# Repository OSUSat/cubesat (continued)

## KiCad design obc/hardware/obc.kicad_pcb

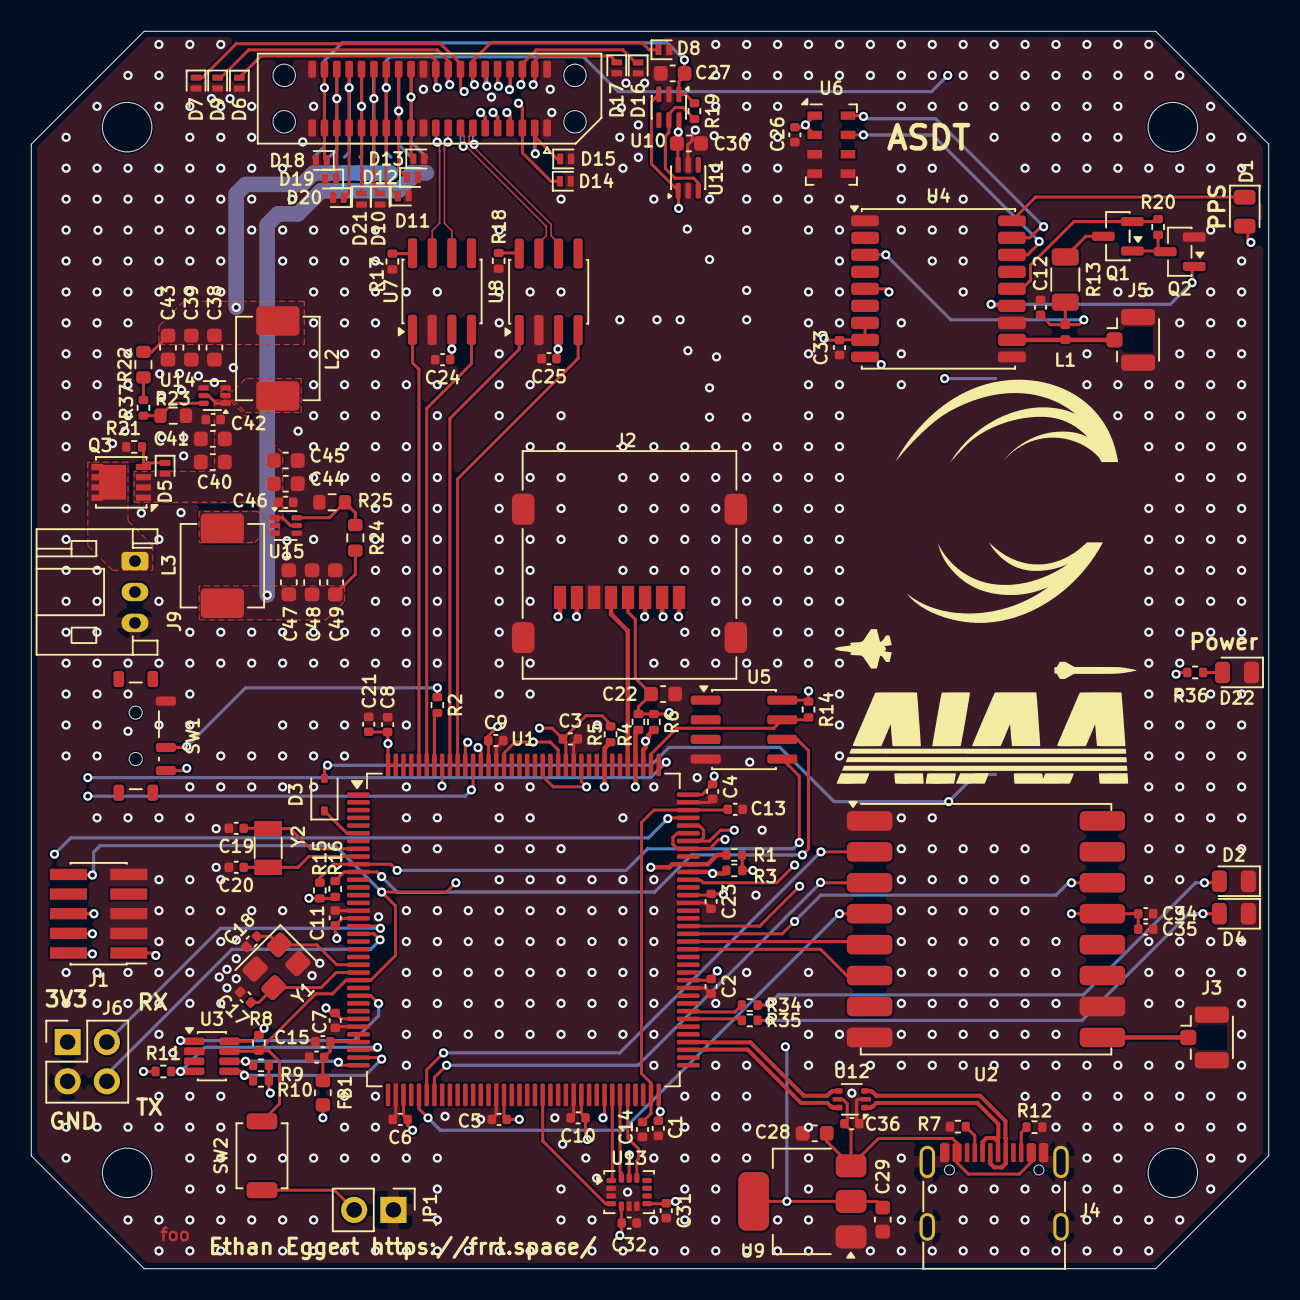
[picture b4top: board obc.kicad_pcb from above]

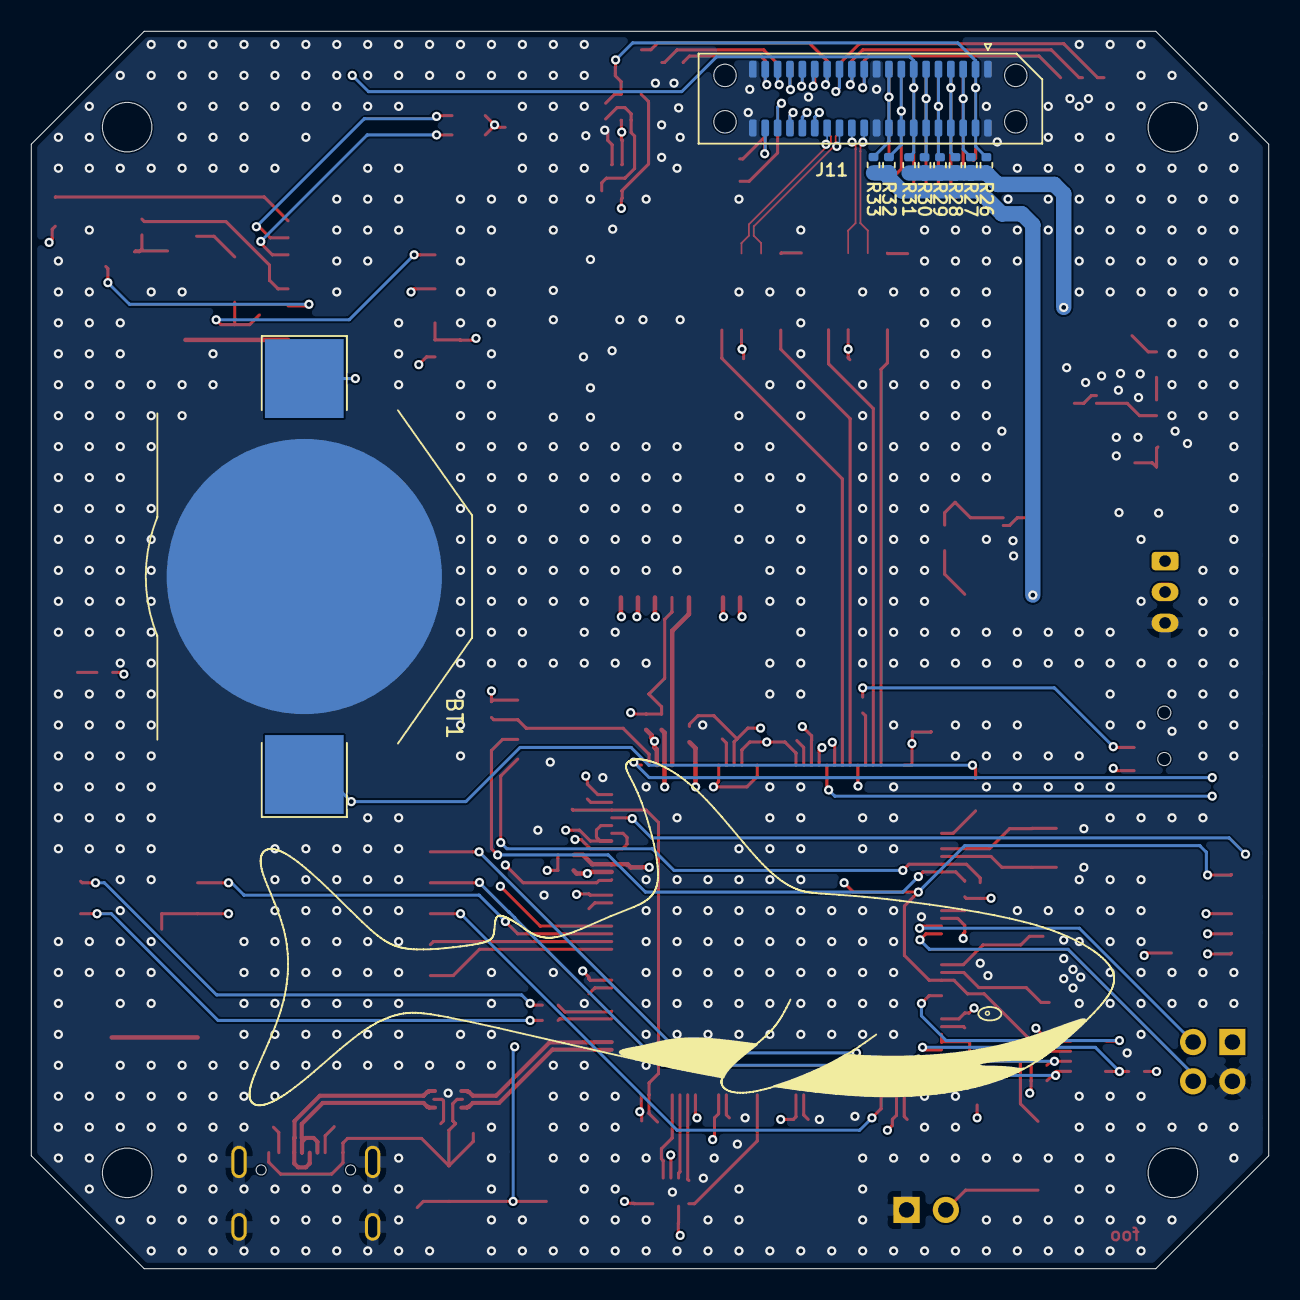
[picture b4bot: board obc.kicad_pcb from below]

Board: 4 copper layers, 80.0 x 80.0 mm, 148 parts (10 on the bottom side), 108 nets.

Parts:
BT1: CR2032; BatteryHolder_Keystone_3002_1x2032
C1, C2, C3, C4, C5, C6, C7, C8, C9, C10, C11, C15, C23, C24, C25, C26, C31, C32, C33, C34, C36, C42, C46: 100nF; C_0402_1005Metric
C12: 10nF; C_0402_1005Metric
C13, C14: 2.2uF; C_0402_1005Metric
C16, C35: 1uF; C_0402_1005Metric
C17, C18: 12pF; C_0402_1005Metric
C19, C20: 15pF; C_0402_1005Metric
C21: 4.7uF; C_0402_1005Metric
C22, C27, C28, C30, C40, C41, C44, C45: 10uF; C_0603_1608Metric
C29, C38, C39, C43, C47, C48, C49: 22u; C_0603_1608Metric
D1: White; LED_0805_2012Metric
D2: Red; LED_0805_2012Metric
D3: 1N5819WS; D_SOD-323
D4: Green; LED_0805_2012Metric
D5: D_TVS; D_SOD-882
D6, D7, D8, D9, D10, D11, D12, D13, D14, D15, D16, D17, D18, D19, D20, D21: D_Zener; D_SOD-882
D22: Yellow; LED_0805_2012Metric
FB1: 600R; L_0603_1608Metric
H1, H2, H3, H4: MountingHole; MountingHole_3.2mm_M3
J1: Conn_ARM_JTAG_SWD_10; PinHeader_2x05_P1.27mm_Vertical_SMD
J2: Micro_SD_Card; microSD_HC_Molex_47219-2001
J3, J5: Conn_Coaxial; U.FL_Hirose_U.FL-R-SMT-1_Vertical
J4: USB_C_Receptacle_USB2.0_16P; USB_C_Receptacle_G-Switch_GT-USB-7010ASV
J6: Conn_02x02_Odd_Even; PinHeader_2x02_P2.54mm_Vertical
J9: Conn_01x03; JST_PH_S3B-PH-K_1x03_P2.00mm_Horizontal
J10: Samtec_ERM8-020-XX.X-DV_2x20_P0.8mm_Terminal
J11: ERF8-020-09.0-L-DV-TR; Samtec_ERF8-020-XX.X-DV_2x20_P0.8mm_Socket
JP1: Jumper; PinHeader_1x02_P2.54mm_Vertical
L1: 27nH; L_0402_1005Metric
L2, L3: 1.5uH; L_Vishay_IHLP-2020
Q1: AO3401A; SOT-23
Q2: AO3400A; SOT-23
Q3: SI7129DN-T1-GE3; Vishay_PowerPAK_1212-8_Single
R1, R3, R4, R5, R6, R17, R18, R20: 51k; R_0402_1005Metric
R2, R8, R9, R10, R11, R14, R15, R16, R19, R21: 10k; R_0402_1005Metric
R7, R12: 5.1k; R_0402_1005Metric
R13: 10; R_1206_3216Metric
R22: 120k; R_0603_1608Metric
R23, R25: 30k; R_0603_1608Metric
R24: 220k; R_0603_1608Metric
R26, R27, R28, R29, R30, R31, R32, R33: 0; R_0402_1005Metric
R34, R35, R36: 1k; R_0402_1005Metric
R37: 15k; R_0402_1005Metric
SW1: SW_SPDT; SW_SPDT_Shouhan_MSK12C02
SW2: SW_Push; SW_SPST_TS-1088-xR020
U1: STM32H743ZGT6; LQFP-144_20x20mm_P0.5mm
U2: RFM96W-433S2; HOPERF_RFM9XW_SMD
U3: MAX6369; SOT-23-8
U4: MAX-M10S; ublox_MAX
U5: FM24CL16B; SOIC-8_3.9x4.9mm_P1.27mm
U6: MS5607-02BA; LGA-8_3x5mm_P1.25mm
U7, U8: SN65HVD230; SOIC-8_3.9x4.9mm_P1.27mm
U9: AMS1117-3.3; SOT-223-3_TabPin2
U10, U11: LM66100DCK; SOT-363_SC-70-6
U12: USBLC6-2P6; SOT-666
U13: ISM6HG256X; LGA-14_3x2.5mm_P0.5mm_LayoutBorder3x4y
U14, U15: TPS564242; SOT-563
Y1: 25 MHz; Crystal_SMD_3225-4Pin_3.2x2.5mm
Y2: 32.768 kHz; Crystal_SMD_3215-2Pin_3.2x1.5mm

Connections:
+3V3: C1.1, C2.1, C3.1, C4.1, C5.1, C6.1, C7.1, C8.1, C9.1, C10.1, C11.1, C21.1, C22.1, C23.1, C24.1, C25.1, C26.1, C30.1, C31.1, C32.1, C33.1, D1.2 (A), FB1.2, J1.1 (VTref), J2.4 (VDD), J6.1, R1.1, R3.1, R4.1, R5.1, R6.1, R8.1, R9.1, R10.1, R11.1, R14.1, R15.1, R16.1, R36.1, SW1.3 (C), U1.17 (VDD), U1.30 (VDD), U1.39 (VDD), U1.52 (VDD), U1.62 (VDD), U1.72 (VDD), U1.84 (VDD), U1.95 (VDD33_USB), U1.108 (VDD), U1.121 (VDD), U1.131 (VDD), U1.143 (PDR_ON), U1.144 (VDD), U3.8 (VCC), U4.7 (VCC_IO), U4.8 (VCC), U5.8 (VDD), U6.1 (VDD), U6.2 (PS), U7.3 (VCC), U8.3 (VCC), U10.6 (VOUT), U11.6 (VOUT), U13.5 (VDDIO), U13.8 (VDD)
+BATT: C40.1, C41.1, C42.1, C44.1, C45.1, C46.1, D5.2 (A2), Q3.1 (S), Q3.2 (S), Q3.3 (S), U14.1 (VIN), U14.5 (EN), U15.1 (VIN), U15.5 (EN)
/Backup Supply/VOUT_3V3: C38.1, C39.1, C43.1, L2.2, R22.1, R26.1, R27.1, R28.1, R29.1, R30.1, R31.1
/Backup Supply/VOUT_5V: C47.1, C48.1, C49.1, L3.2, R24.1, R32.1, R33.1
/Inter-Board-Connector/CAN_AUX+: J10.15, J11.26, U8.7 (CANH)
/Inter-Board-Connector/CAN_AUX-: J10.13, J11.28, U8.6 (CANL)
/Inter-Board-Connector/CAN_MAIN+: J10.19, J11.22, U7.7 (CANH)
/Inter-Board-Connector/CAN_MAIN-: J10.17, J11.24, U7.6 (CANL)
/Inter-Board-Connector/EPS_PGOOD: D6.1 (K), J10.20, J11.21, U1.137 (PB7)
/Inter-Board-Connector/OBC_EPS_RESET: D7.1 (K), J10.16, J11.25, U1.134 (PB4)
/Inter-Board-Connector/OBC_HEARTBEAT: D8.1 (K), J10.14, J11.27, U1.132 (PG15)
/Inter-Board-Connector/RAIL_1_VOUT: C27.1, D18.1 (K), J10.37, J10.38, J11.3, J11.4, R19.1, R26.2, U10.1 (VIN)
/Inter-Board-Connector/RAIL_2_VOUT: D19.1 (K), J10.35, J10.36, J11.5, J11.6, R27.2
/Inter-Board-Connector/RAIL_3_VOUT: D20.1 (K), J10.33, J10.34, J11.7, J11.8, R28.2
/Inter-Board-Connector/RAIL_4_VOUT: D21.1 (K), J10.31, J10.32, J11.9, J11.10, R29.2
/Inter-Board-Connector/RAIL_5_VOUT: D10.1 (K), J10.29, J10.30, J11.11, J11.12, R30.2
/Inter-Board-Connector/RAIL_7_VOUT: D12.1 (K), J10.25, J10.26, J11.15, J11.16, R32.2
/Inter-Board-Connector/RAIL_8_VOUT: D13.1 (K), J10.23, J10.24, J11.17, J11.18, R33.2
/Inter-Board-Connector/SYSTEM_AUX_UART_RX: D14.1 (K), J10.5, J11.36, U1.119 (PD5), U1.124 (PG9)
/Inter-Board-Connector/SYSTEM_AUX_UART_TX: D15.1 (K), J10.3, J11.38, U1.122 (PD6), U1.129 (PG14)
/Inter-Board-Connector/SYSTEM_MAIN_UART_RX: D16.1 (K), J10.6, J11.35, U1.101 (PA9), U1.103 (PA11)
/Inter-Board-Connector/SYSTEM_MAIN_UART_TX: D17.1 (K), J10.4, J11.37, U1.102 (PA10), U1.104 (PA12)
/Inter-Board-Connector/UNUSED_1: J10.12, J11.29
/Inter-Board-Connector/UNUSED_2: J10.10, J11.31
/Inter-Board-Connector/UNUSED_3: J10.8, J11.33
/Inter-Board-Connector/UNUSED_4: J10.11, J11.30
/Inter-Board-Connector/UNUSED_5: J10.9, J11.32
/Inter-Board-Connector/UNUSED_6: J10.7, J11.34
/STM32H7/BOOT0: R2.2, U1.138 (BOOT0)
/STM32H7/CAN/CAN1_RX: U1.139 (PB8), U7.4 (R)
/STM32H7/CAN/CAN1_TX: U1.140 (PB9), U7.1 (D)
/STM32H7/CAN/CAN2_RX: U1.135 (PB5), U8.4 (R)
/STM32H7/CAN/CAN2_TX: U1.136 (PB6), U8.1 (D)
/STM32H7/FRAM_WP: R14.2, U1.110 (PA15), U5.7 (WP)
/STM32H7/GPS_EXTINT: U1.91 (PG6), U4.5 (EXTINT)
/STM32H7/IMU_INT: U1.57 (PG1), U13.4 (INT1)
/STM32H7/RADIO_DIO0: U1.90 (PG5), U2.14 (DIO0)
/STM32H7/RTC_I: C19.1, U1.8 (PC14), Y2.2
/STM32H7/RTC_O: C20.1, U1.9 (PC15), Y2.1
/STM32H7/Radio/LORA_ANT: J3.1 (In), U2.9 (ANT)
/STM32H7/SD_CK: J2.5 (CLK), U1.113 (PC12)
/STM32H7/SD_CMD: J2.3 (CMD), R5.2, U1.116 (PD2)
/STM32H7/SD_D0: J2.7 (DAT0), R3.2, U1.98 (PC8)
/STM32H7/SD_D1: J2.8 (DAT1), R1.2, U1.99 (PC9)
/STM32H7/SD_D2: J2.1 (DAT2), R6.2, U1.111 (PC10)
/STM32H7/SD_D3: J2.2 (DAT3/CD), R4.2, U1.112 (PC11)
/STM32H7/SPI1_MISO: U1.42 (PA6), U2.2 (MISO)
/STM32H7/SPI1_MOSI: U1.43 (PA7), U2.3 (MOSI)
/STM32H7/SPI1_SCK: U1.41 (PA5), U2.4 (SCK)
/STM32H7/SPI4_MISO: U1.66 (PE13), U13.1 (SDO/SA0)
/STM32H7/SPI4_MOSI: U1.67 (PE14), U13.14 (SDA)
/STM32H7/SPI4_SCK: U1.65 (PE12), U13.13 (SCL)
/STM32H7/SWCLK: J1.4 (SWCLK/TCK), U1.109 (PA14)
/STM32H7/SWDIO: J1.2 (SWDIO/TMS), U1.105 (PA13)
/STM32H7/SWTRACE: J1.6 (SWO/TDO), U1.133 (PB3)
/STM32H7/Sensors/GNSS_ANT: J5.1 (In), L1.1, U4.11 (RF_IN)
/STM32H7/Sensors/~ANT_SHORT: C12.1, L1.2, R13.2, U4.3 (RXD)
/STM32H7/Sensors/~IMU_CS: U1.68 (PE15), U13.12 (CS)
/STM32H7/UART3_RX: J6.2, U1.18 (PF6)
/STM32H7/UART3_TX: J6.4, U1.19 (PF7)
/STM32H7/USB_D+: U1.76 (PB15), U12.4 (I/O2)
/STM32H7/USB_D-: U1.75 (PB14), U12.6 (I/O1)
/STM32H7/WDI: U1.27 (PC1), U3.1 (WDI)
/STM32H7/WD_S0: R11.2, U1.34 (PA0), U3.4 (SET0)
/STM32H7/WD_S1: R10.2, U1.35 (PA1), U3.5 (SET1)
/STM32H7/WD_S2: R9.2, U1.36 (PA2), U3.6 (SET2)
/STM32H7/~GPS_RESET: U1.97 (PC7), U4.9 (~RESET)
/STM32H7/~RADIO_CS: U1.89 (PG4), U2.5 (NSS)
/STM32H7/~RADIO_RESET: U1.88 (PG3), U2.6 (RESET)
/STM32H7/~RESET: D9.1 (K), J1.10 (~RESET), J10.18, J11.23, R8.2, SW2.2, U1.25 (NRST), U3.7 (~WDO)
/UNPROT_USB_D+: J4.A6 (D+), J4.B6 (D+), U12.3 (I/O2)
/UNPROT_USB_D-: J4.A7 (D-), J4.B7 (D-), U12.1 (I/O1)
GND: BT1.2 (-), C1.2, C2.2, C3.2, C4.2, C5.2, C6.2, C7.2, C8.2, C9.2, C10.2, C11.2, C12.2, C13.2, C14.2, C15.2, C16.2, C17.2, C18.2, C19.2, C20.2, C21.2, C22.2, C23.2, C24.2, C25.2, C26.2, C27.2, C28.2, C29.2, C30.2, C31.2, C32.2, C33.2, C34.2, C35.2, C36.2, C38.2, C39.2, C40.2, C41.2, C42.2, C43.2, C44.2, C45.2, C46.2, C47.2, C48.2, C49.2, D2.1 (K), D4.1 (K), D6.2 (A), D7.2 (A), D8.2 (A), D9.2 (A), D10.2 (A), D11.2 (A), D12.2 (A), D13.2 (A), D14.2 (A), D15.2 (A), D16.2 (A), D17.2 (A), D18.2 (A), D19.2 (A), D20.2 (A), D21.2 (A), D22.1 (K), J1.3 (GND), J1.5 (GND), J1.9 (GNDDetect), J2.6 (VSS), J2.SH (SHIELD), J3.2 (Ext), J4.A1 (GND), J4.A12 (GND), J4.B1 (GND), J4.B12 (GND), J4.SH (SHIELD), J5.2 (Ext), J6.3, J9.3, J10.1, J10.2, J10.21, J10.22, J10.39, J10.40, J11.1, J11.2, J11.19, J11.20, J11.39, J11.40, JP1.1 (A), Q2.2 (S), R7.2, R12.1, R17.2, R18.2, R21.2, R23.2, R25.2, SW1.1 (A), U1.16 (VSS), U1.31 (VSSA), U1.38 (VSS), U1.51 (VSS), U1.61 (VSS), U1.83 (VSS), U1.94 (VSS), U1.107 (VSS), U1.120 (VSS), U1.130 (VSS), U2.1 (GND), U2.8 (GND), U2.10 (GND), U3.2 (GND), U4.1 (GND), U4.10 (GND), U4.12 (GND), U5.4 (VSS), U6.3 (GND), U6.4 (CSB), U6.5 (CSB), U7.2 (GND), U8.2 (GND), U9.1 (GND), U10.2 (GND), U11.2 (GND), U11.5 (ST), U12.2 (GND), U13.2 (SDX), U13.3 (SCX), U13.6 (GND), U13.7 (GND), U14.3 (GND), U14.4 (AGND), U15.3 (GND), U15.4 (AGND), Y1.2 (G), Y1.4 (G)
unnamed: BT1.1 (+), D3.2 (A)
unnamed: C13.1, C14.1, U1.71 (VCAP), U1.106 (VCAP)
unnamed: D1.1 (K), U4.18 (~SAFEBOOT)
unnamed: D2.2 (A), R34.2
unnamed: D3.1 (K), U1.6 (VBAT)
unnamed: D4.2 (A), R35.2
unnamed: D5.1 (A1), Q3.4 (G), R21.1
unnamed: D22.2 (A), R36.2
unnamed: J4.A5 (CC1), R7.1
unnamed: J4.B5 (CC2), R12.2
unnamed: J9.1, Q3.5 (D)
unnamed: JP1.2 (B), SW2.1
unnamed: Q1.3 (D), R13.1
unnamed: Q1.1 (G), Q2.3 (D), R20.2
unnamed: Q1.2 (S), R20.1, U4.14 (VCC_RF)
unnamed: Q2.1 (G), U4.13 (LNA_EN)
unnamed: R22.2, R37.1
unnamed: R2.1, SW1.2 (B)
unnamed: R35.1, U1.79 (PD10)
unnamed: R34.1, U1.80 (PD11)
unnamed: C18.1, U1.23 (PH0), Y1.1
unnamed: C17.1, U1.24 (PH1), Y1.3
unnamed: R17.1, U7.8 (Rs)
unnamed: R18.1, U8.8 (Rs)
unnamed: R19.2, U10.5 (ST), U11.3 (~CE)
unnamed: C29.1, U9.2 (VO), U10.3 (~CE), U11.1 (VIN)
unnamed: R23.1, R37.2, U14.6 (FB)
unnamed: L2.1, U14.2 (SW)
unnamed: R24.2, R25.1, U15.6 (FB)
unnamed: L3.1, U15.2 (SW)
SCL: R16.2, U1.11 (PF1), U4.17 (SCL), U5.6 (SCL), U6.8 (SCLK)
SDA: R15.2, U1.10 (PF0), U4.16 (SDA), U5.5 (SDA), U6.7 (SDI/SDA)
VBUS: C28.1, C36.1, J4.A4 (VBUS), J4.A9 (VBUS), J4.B4 (VBUS), J4.B9 (VBUS), U9.3 (VI), U12.5 (VBUS)
VDDA: C15.1, C16.1, FB1.1, U1.32 (VREF+), U1.33 (VDDA)
VDD_RADIO: C34.1, C35.1, D11.1 (K), J10.27, J10.28, J11.13, J11.14, R31.2, U2.13 (3.3V)

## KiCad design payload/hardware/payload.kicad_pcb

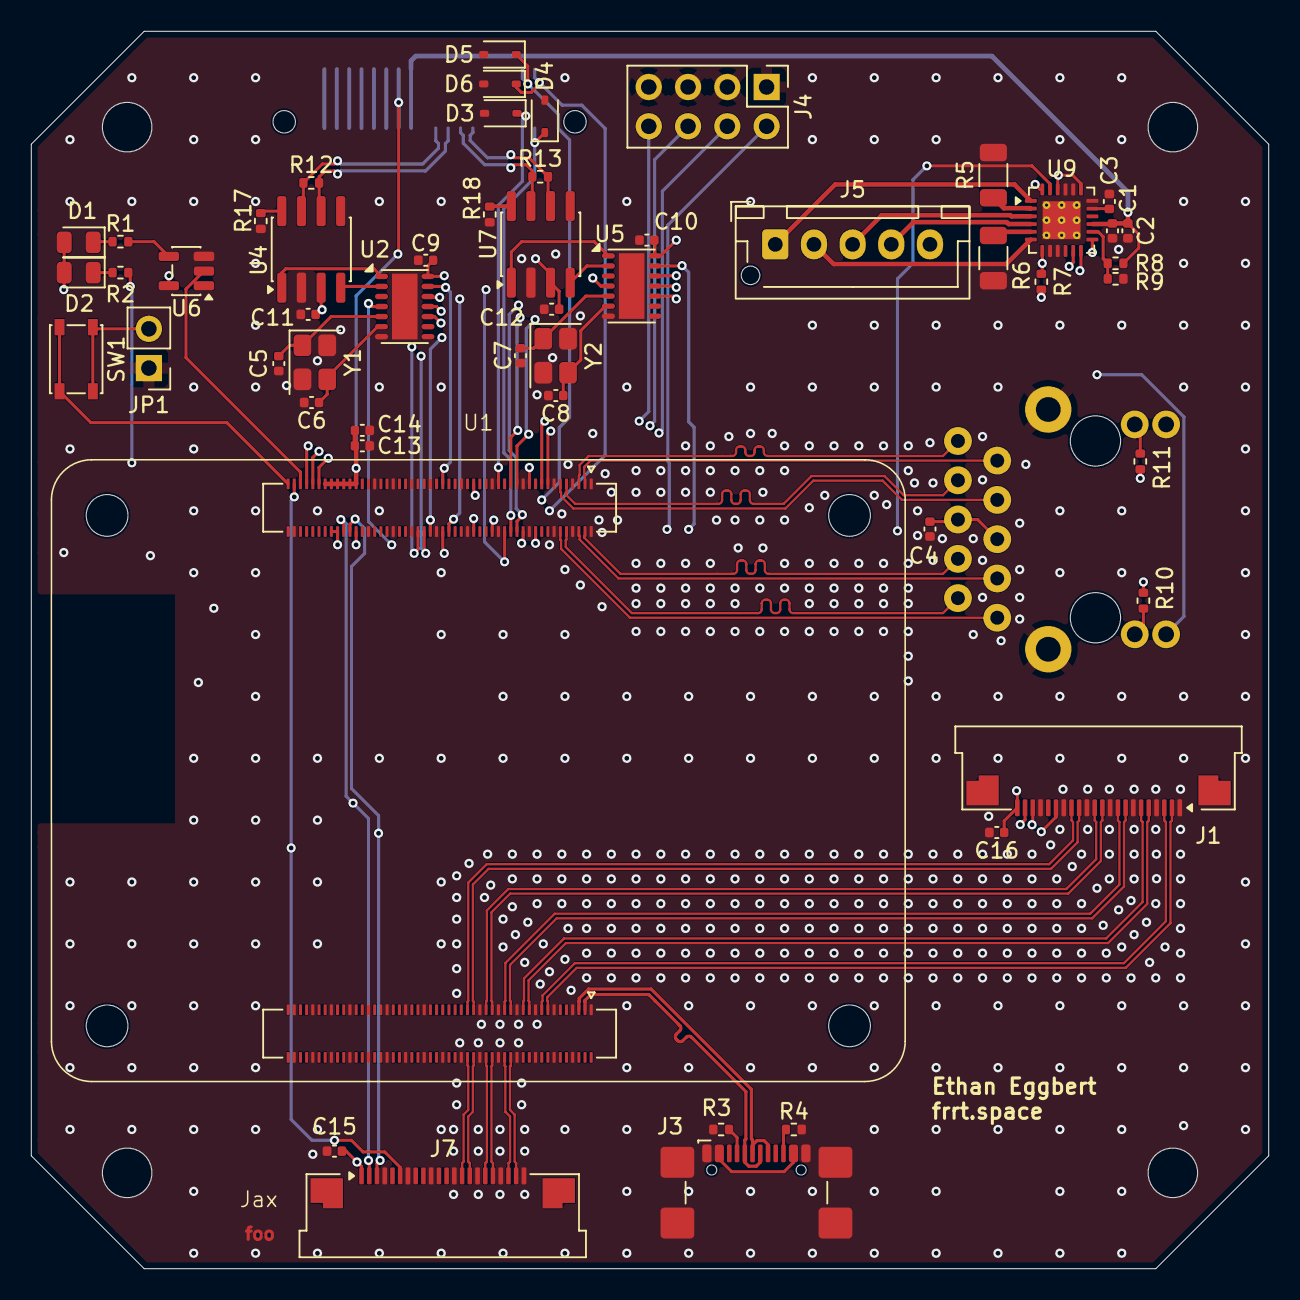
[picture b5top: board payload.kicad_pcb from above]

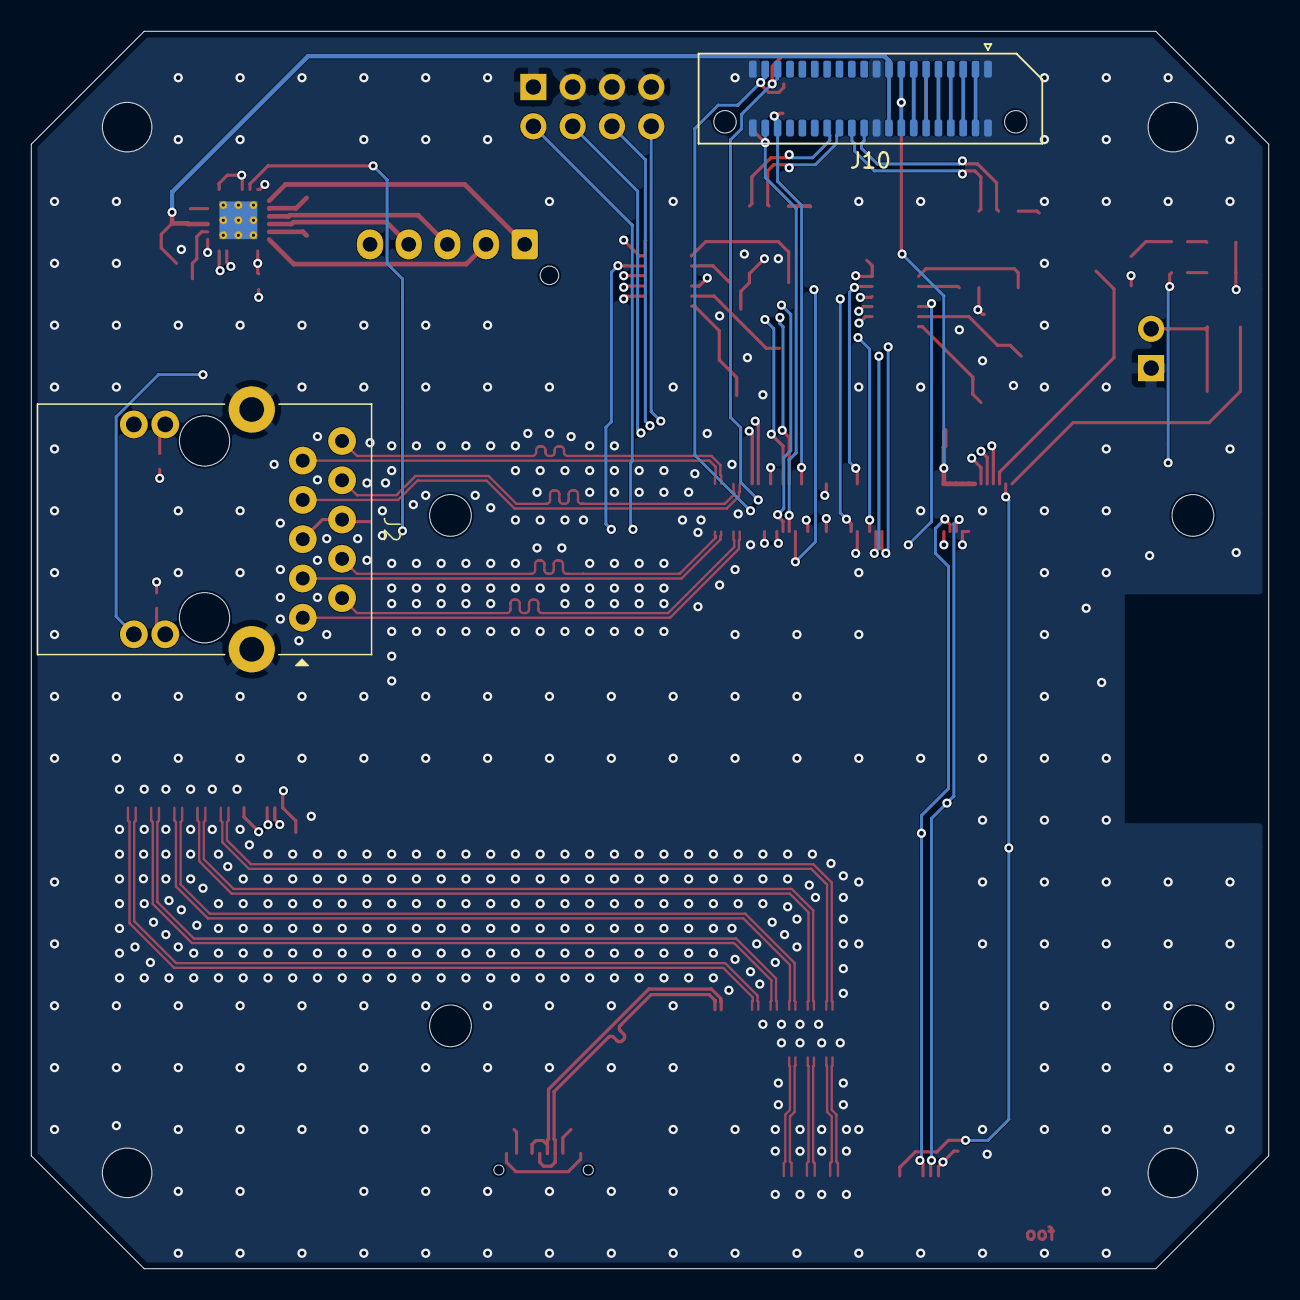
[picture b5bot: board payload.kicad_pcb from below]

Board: 4 copper layers, 80.0 x 80.0 mm, 55 parts (2 on the bottom side), 96 nets.

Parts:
C1, C4, C9, C10, C11, C12, C13, C15, C16: 100n; C_0402_1005Metric
C2: 10u; C_0402_1005Metric
C3: 2.2u; C_0402_1005Metric
C5, C6, C7, C8: TBD; C_0402_1005Metric
C14: 1u; C_0402_1005Metric
D1, D2: LED; LED_0805_2012Metric
D3, D4, D5, D6: D_Zener; D_SOD-323
J1: Amphenol_F32Q-1A7x1-11022_1x22-1MP_P0.5mm_Horizontal
J2: ARJM11C7-502-AB; ARJM11C7-502-LEDs
J3: USB_C_Receptacle_USB2.0_16P; USB_C_Receptacle_GCT_USB4110
J4: Conn_02x04_Odd_Even; PinHeader_2x04_P2.54mm_Vertical
J5: Conn_01x05; JST_XH_B5B-XH-AM_1x05_P2.50mm_Vertical
J7: Amphenol_F32R-1A7x1-11022_1x22-1MP_P0.5mm_Horizontal
J10: Conn_02x20_Odd_Even; Samtec_ERF8-020-XX.X-DV_2x20_P0.8mm_Socket
JP1: Jumper_2_Open; PinHeader_1x02_P2.54mm_Vertical
R1, R2, R10, R11: 1k; R_0402_1005Metric
R3, R4, R7: 5.1k; R_0402_1005Metric
R5, R6: 1; R_1206_3216Metric
R8: 12k; R_0402_1005Metric
R9: 2k; R_0402_1005Metric
R12, R13: 120; R_0402_1005Metric
R17, R18: 51k; R_0402_1005Metric
SW1: SW_Push; SW_SPST_PTS810
U1: CM4; Module_Raspberry_Pi_CM4
U2, U5: MCP2517FD-xJHA; DFN-14-1EP_3x4.5mm_P0.65mm_EP1.65x4.25mm
U4, U7: SN65HVD230; SOIC-8_3.9x4.9mm_P1.27mm
U6: 74LVC1G07; SOT-23-5
U9: DRV8846; VQFN-24-1EP_4x4mm_P0.5mm_EP2.45x2.45mm_ThermalVias
Y1, Y2: 20 MHz; Crystal_SMD_SeikoEpson_TSX3225-4Pin_3.2x2.5mm

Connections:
+3V3: C9.1, C10.1, C11.1, C12.1, C15.1, C16.1, D1.2 (A), D2.2 (A), J1.22 (3V3), J7.1 (3V3), R7.1, R10.2, R11.1, U1.78 (GPIO_VREF), U1.84 (CM4_3.3V), U1.86 (CM4_3.3V), U2.14 (VDD), U4.3 (VCC), U5.14 (VDD), U6.5 (VCC), U7.3 (VCC), U9.19 (ADEC), U9.22 (DEC0), U9.24 (DEC1)
+5V: C13.1, C14.1, J10.15, J10.16, U1.77 (+5V), U1.79 (+5V), U1.81 (+5V), U1.83 (+5V), U1.85 (+5V), U1.87 (+5V)
/CM4/CAN1+: J10.22, R12.1, U4.7 (CANH)
/CM4/CAN1-: J10.24, R12.2, U4.6 (CANL)
/CM4/CAN1_INT: U1.24 (GPIO26), U2.4 (~INT)
/CM4/CAN2+: J10.26, R13.1, U7.7 (CANH)
/CM4/CAN2-: J10.28, R13.2, U7.6 (CANL)
/CM4/CAN2_INT: U1.48 (GPIO27), U5.4 (~INT)
/CM4/Cameras/CAM0_C+: J7.14 (CAM_C+), U1.142 (CAM0_C_P)
/CM4/Cameras/CAM0_C-: J7.15 (CAM_C-), U1.140 (CAM0_C_N)
/CM4/Cameras/CAM0_D0+: J7.20 (CAM_D0+), U1.130 (CAM0_D0_P)
/CM4/Cameras/CAM0_D0-: J7.21 (CAM_D0-), U1.128 (CAM0_D0_N)
/CM4/Cameras/CAM0_D1+: J7.17 (CAM_D1+), U1.136 (CAM0_D1_P)
/CM4/Cameras/CAM0_D1-: J7.18 (CAM_D1-), U1.134 (CAM0_D1_N)
/CM4/Cameras/CAM1_C+: J1.9 (CAM_C+), U1.129 (CAM1_C_P)
/CM4/Cameras/CAM1_C-: J1.8 (CAM_C-), U1.127 (CAM1_C_N)
/CM4/Cameras/CAM1_D0+: J1.3 (CAM_D0+), U1.117 (CAM1_D0_P)
/CM4/Cameras/CAM1_D0-: J1.2 (CAM_D0-), U1.115 (CAM1_D0_N)
/CM4/Cameras/CAM1_D1+: J1.6 (CAM_D1+), U1.123 (CAM1_D1_P)
/CM4/Cameras/CAM1_D1-: J1.5 (CAM_D1-), U1.121 (CAM1_D1_N)
/CM4/Cameras/CAM1_D2+: J1.12 (CAM_D2+), U1.135 (CAM1_D2_P)
/CM4/Cameras/CAM1_D2-: J1.11 (CAM_D2-), U1.133 (CAM1_D2_N)
/CM4/Cameras/CAM1_D3+: J1.15 (CAM_D3+), U1.141 (CAM1_D3_P)
/CM4/Cameras/CAM1_D3-: J1.14 (CAM_D3-), U1.139 (CAM1_D3_N)
/CM4/Cameras/CAMERA_GPIO: J1.17 (CAM_IO0), J7.6 (CAM_IO0), U1.97 (Camera_GPIO)
/CM4/Cameras/CAMERA_SCL: J1.20 (SCL), J7.3 (SCL), U1.80 (SCL0)
/CM4/Cameras/CAMERA_SDA: J1.21 (SDA), J7.2 (SDA), U1.82 (SDA0)
/CM4/ETH_LED1: J2.14, U1.15 (Ethernet_nLED3)
/CM4/ETH_LED2: J2.12, U1.17 (Ethernet_nLED2)
/CM4/ETH_P0+: J2.1 (TD1+), U1.12 (Ethernet_P0_P)
/CM4/ETH_P0-: J2.2 (TD1-), U1.10 (Ethernet_P0_N)
/CM4/ETH_P1+: J2.4 (TD2-), U1.4 (Ethernet_P1_P)
/CM4/ETH_P1-: J2.3 (TD2+), U1.6 (Ethernet_P1_N)
/CM4/ETH_P2+: J2.7 (TD3+), U1.11 (Ethernet_P2_P)
/CM4/ETH_P2-: J2.8 (TD3-), U1.9 (Ethernet_P2_N)
/CM4/ETH_P3+: J2.9 (TD4+), U1.3 (Ethernet_P3_P)
/CM4/ETH_P3-: J2.10 (TD4-), U1.5 (Ethernet_P3_N)
/CM4/MOTOR_DIR: U1.56 (GPIO3), U9.13 (DIR)
/CM4/MOTOR_STEP: U1.58 (GPIO2), U9.12 (STEP)
/CM4/POWER_BUTTON: SW1.2, U1.99 (GLOBAL_EN)
/CM4/UART1_RX: D6.1 (K), J10.37, U1.40 (GPIO9)
/CM4/UART1_TX: D5.1 (K), J10.35, U1.39 (GPIO8)
/CM4/UART2_RX: D4.1 (K), J10.38, U1.28 (GPIO13)
/CM4/UART2_TX: D3.1 (K), J10.36, U1.31 (GPIO12)
/CM4/USB_D+: J3.A6 (D+), J3.B6 (D+), U1.105 (USB_P)
/CM4/USB_D-: J3.A7 (D-), J3.B7 (D-), U1.103 (USB_N)
/CM4/~CAN1_CS: U1.49 (GPIO18), U2.13 (~CS)
/CM4/~CAN2_CS: U1.50 (GPIO17), U5.13 (~CS)
/CM4/~MOTOR_EN: U1.54 (GPIO4), U9.11 (~ENBL)
/CM4/~MOTOR_FAULT: R7.2, U1.30 (GPIO6), U9.7 (~FAULT)
/CM4/~MOTOR_SLEEP: U1.34 (GPIO5), U9.23 (~SLEEP)
/Inter Board Connector/RAIL_1_VOUT: J10.3, J10.4
/Inter Board Connector/RAIL_2_VOUT: J10.5, J10.6
/Inter Board Connector/RAIL_3_VOUT: J10.7, J10.8
/Inter Board Connector/RAIL_4_VOUT: J10.9, J10.10
/Inter Board Connector/RAIL_5_VOUT: J10.11, J10.12
/Inter Board Connector/RAIL_6_VOUT: J10.13, J10.14
/Inter Board Connector/RAIL_8_VOUT: C1.1, C2.1, J10.17, J10.18, R8.1, U9.15 (VM)
GND: C1.2, C2.2, C3.2, C4.2, C5.2, C6.2, C7.2, C8.2, C9.2, C10.2, C11.2, C12.2, C13.2, C14.2, C15.2, C16.2, D3.2 (A), D4.2 (A), D5.2 (A), D6.2 (A), J1.1 (GND), J1.4 (GND), J1.7 (GND), J1.10 (GND), J1.13 (GND), J1.16 (GND), J1.19 (GND), J2.SH, J3.A1 (GND), J3.A12 (GND), J3.B1 (GND), J3.B12 (GND), J3.SH (SHIELD), J4.1, J4.3, J4.5, J4.7, J7.4 (GND), J7.7 (GND), J7.10 (GND), J7.13 (GND), J7.16 (GND), J7.19 (GND), J7.22 (GND), J10.1, J10.2, J10.19, J10.20, J10.39, J10.40, JP1.1 (A), R3.2, R4.2, R5.2, R6.2, R9.2, R17.2, R18.2, U1.1 (GND), U1.2 (GND), U1.7 (GND), U1.8 (GND), U1.13 (GND), U1.14 (GND), U1.22 (GND), U1.23 (GND), U1.32 (GND), U1.33 (GND), U1.42 (GND), U1.43 (GND), U1.52 (GND), U1.53 (GND), U1.59 (GND), U1.60 (GND), U1.65 (GND), U1.66 (GND), U1.71 (GND), U1.74 (GND), U1.98 (GND), U1.101 (USB_OTG_ID), U1.107 (GND), U1.108 (GND), U1.113 (GND), U1.114 (GND), U1.119 (GND), U1.120 (GND), U1.125 (GND), U1.126 (GND), U1.131 (GND), U1.132 (GND), U1.137 (GND), U1.138 (GND), U1.144 (GND), U1.150 (GND), U1.155 (GND), U1.156 (GND), U1.161 (GND), U1.162 (GND), U1.167 (GND), U1.168 (GND), U1.173 (GND), U1.174 (GND), U1.179 (GND), U1.180 (GND), U1.185 (GND), U1.186 (GND), U1.191 (GND), U1.192 (GND), U1.197 (GND), U1.198 (GND), U2.7 (VSS), U2.15 (VSS), U4.2 (GND), U5.7 (VSS), U5.15 (VSS), U6.3 (GND), U7.2 (GND), U9.8 (M0), U9.9 (M1), U9.18 (GND), U9.20 (I0), U9.21 (I1), U9.25 (GND), Y1.2 (G), Y1.4 (G), Y2.2 (G), Y2.4 (G)
MISO: U1.26 (GPIO19), U2.12 (SDO), U5.12 (SDO)
MOSI: U1.27 (GPIO20), U2.11 (SDI), U5.11 (SDI)
unnamed: C4.1, J2.5 (CT), J2.6 (CT)
unnamed: D1.1 (K), R1.1
unnamed: D2.1 (K), R2.1
unnamed: J2.11, R11.2
unnamed: J2.13, R10.1
unnamed: J3.A5 (CC1), R3.1
unnamed: J3.B5 (CC2), R4.1
unnamed: J3.A4 (VBUS), J3.A9 (VBUS), J3.B4 (VBUS), J3.B9 (VBUS)
unnamed: J4.2, U1.20 (EEPROM_nWP)
unnamed: J4.4, U1.89 (WL_nDisable)
unnamed: J4.6, U1.91 (BT_nDisable)
unnamed: J4.8, U1.93 (nRPIBOOT)
unnamed: J5.1, U9.1 (AOUT1)
unnamed: J5.2, U9.6 (BOUT1)
unnamed: J5.3, U9.3 (AOUT2)
unnamed: J5.4, U9.4 (BOUT2)
unnamed: JP1.2 (B), SW1.1
unnamed: R1.2, U6.4
unnamed: U1.95 (PI_LED_nPWR), U6.2
unnamed: R2.2, U1.21 (Pi_nLED_Activity)
unnamed: C6.1, U2.6 (OSC1), Y1.3
unnamed: C5.1, U2.5 (OSC2), Y1.1
unnamed: U2.2 (RXCAN), U4.4 (R)
unnamed: U2.1 (TXCAN), U4.1 (D)
unnamed: R17.1, U4.8 (Rs)
unnamed: C8.1, U5.6 (OSC1), Y2.3
unnamed: C7.1, U5.5 (OSC2), Y2.1
unnamed: U5.2 (RXCAN), U7.4 (R)
unnamed: U5.1 (TXCAN), U7.1 (D)
unnamed: R18.1, U7.8 (Rs)
unnamed: R5.1, U9.2 (AISEN)
unnamed: R6.1, U9.5 (BISEN)
unnamed: C3.1, U9.17 (VINT)
unnamed: R8.2, R9.1, U9.14 (VREF)
SCK: U1.25 (GPIO21), U2.10 (SCK), U5.10 (SCK)
